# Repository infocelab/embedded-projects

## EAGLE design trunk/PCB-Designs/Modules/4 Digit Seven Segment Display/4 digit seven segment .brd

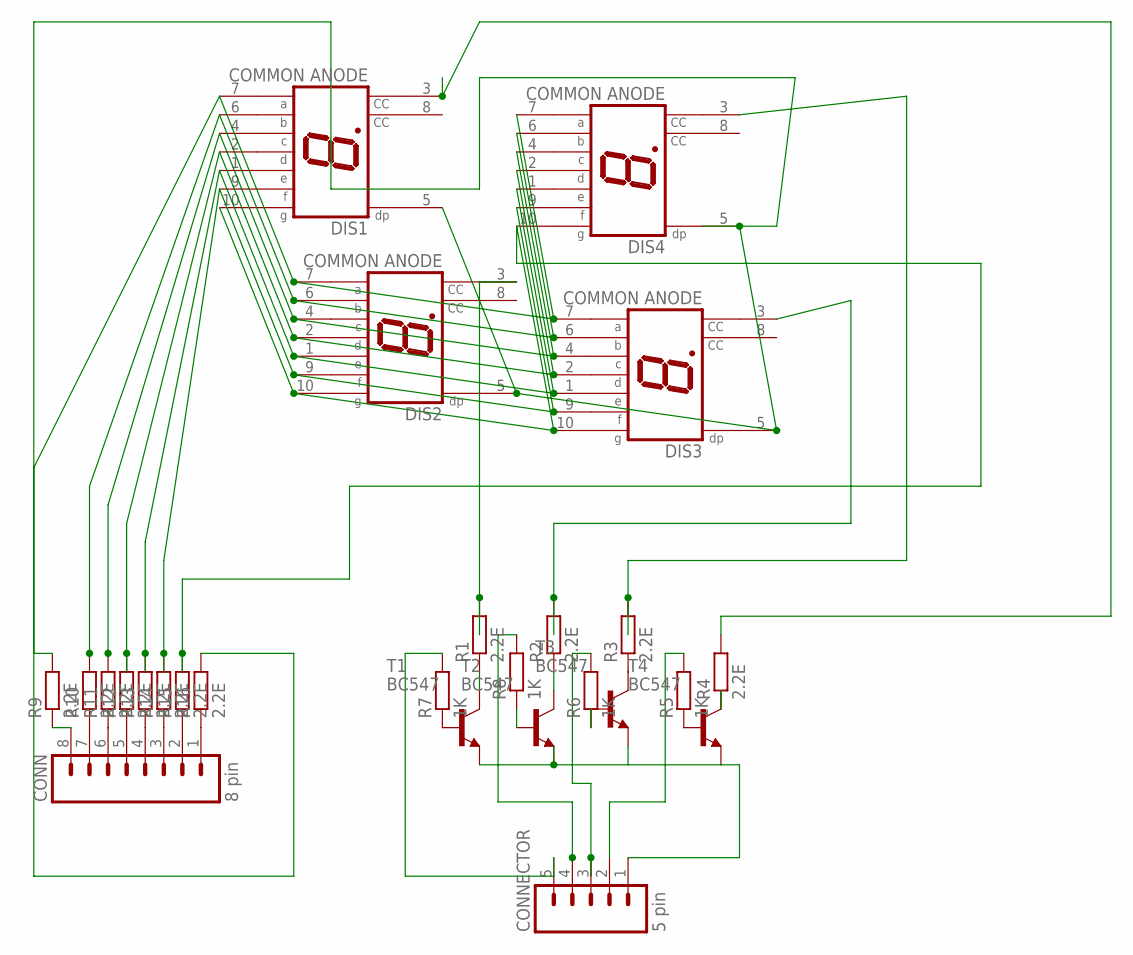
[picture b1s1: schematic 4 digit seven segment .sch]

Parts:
CONN: 8 pin; 08P
CONNECTOR: 5 pin; 05P
DIS1, DIS2, DIS3, DIS4: COMMON ANODE; HDSP-M
R1, R2, R3, R4, R9, R10, R11, R12, R13, R14, R15, R16: 2.2E; 0204/7
R5, R6, R7, R8: 1K; 0204/7
T1, T2, T3, T4: BC547; TO92

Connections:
unnamed: CONNECTOR.4, R8.2
unnamed: DIS1.9 (F), DIS2.9 (F), DIS3.9 (F), DIS4.9 (F), R14.2
unnamed: DIS1.2 (D), DIS2.2 (D), DIS3.2 (D), DIS4.2 (D), R12.2
unnamed: DIS1.6 (B), DIS2.6 (B), DIS3.6 (B), DIS4.6 (B), R10.2
unnamed: DIS1.7 (A), DIS2.7 (A), DIS3.7 (A), DIS4.7 (A), R9.2
unnamed: DIS3.3 (CC), R2.2
unnamed: DIS1.4 (C), DIS2.4 (C), DIS3.4 (C), DIS4.4 (C), R11.2
unnamed: DIS1.1 (E), DIS2.1 (E), DIS3.1 (E), DIS4.1 (E), R13.2
unnamed: CONNECTOR.3, R6.2
unnamed: R1.1, T1.3 (C)
unnamed: R2.1, T2.3 (C)
unnamed: R3.1, T3.3 (C)
unnamed: R4.1, T4.3 (C)
unnamed: R5.1, T4.2 (B)
unnamed: R6.1, T3.2 (B)
unnamed: R7.1, T1.2 (B)
unnamed: R8.1, T2.2 (B)
unnamed: CONN.8, R9.1
unnamed: CONN.7, R10.1
unnamed: CONN.6, R11.1
unnamed: CONN.4, R13.1
unnamed: CONN.3, R14.1
unnamed: CONN.2, R15.1
unnamed: CONN.1, R16.1
unnamed: CONN.5, R12.1
unnamed: DIS1.10 (G), DIS2.10 (G), DIS3.10 (G), DIS4.10 (G), R15.2
unnamed: DIS1.5 (DP), DIS2.5 (DP), DIS3.5 (DP), DIS4.5 (DP), R16.2
unnamed: CONNECTOR.5, R7.2
unnamed: CONNECTOR.2, R5.2
unnamed: CONNECTOR.1, T1.1 (E), T2.1 (E), T3.1 (E), T4.1 (E)
unnamed: DIS1.3 (CC), R4.2
unnamed: DIS4.3 (CC), R3.2
unnamed: DIS2.3 (CC), R1.2

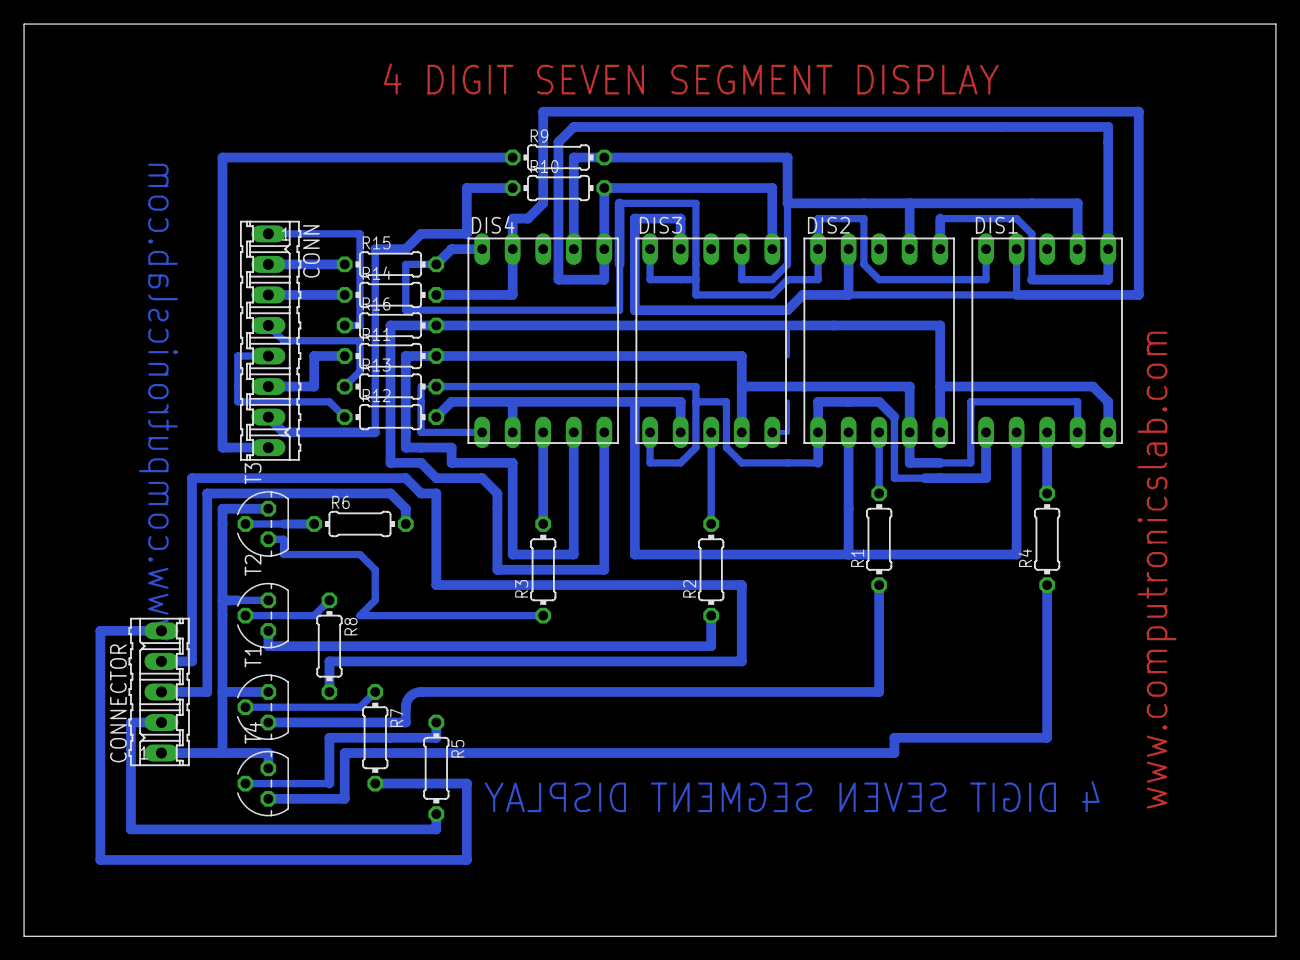
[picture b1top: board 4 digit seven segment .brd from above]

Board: 2 copper layers, 104.1 x 75.9 mm, 26 parts (0 on the bottom side), 33 nets.

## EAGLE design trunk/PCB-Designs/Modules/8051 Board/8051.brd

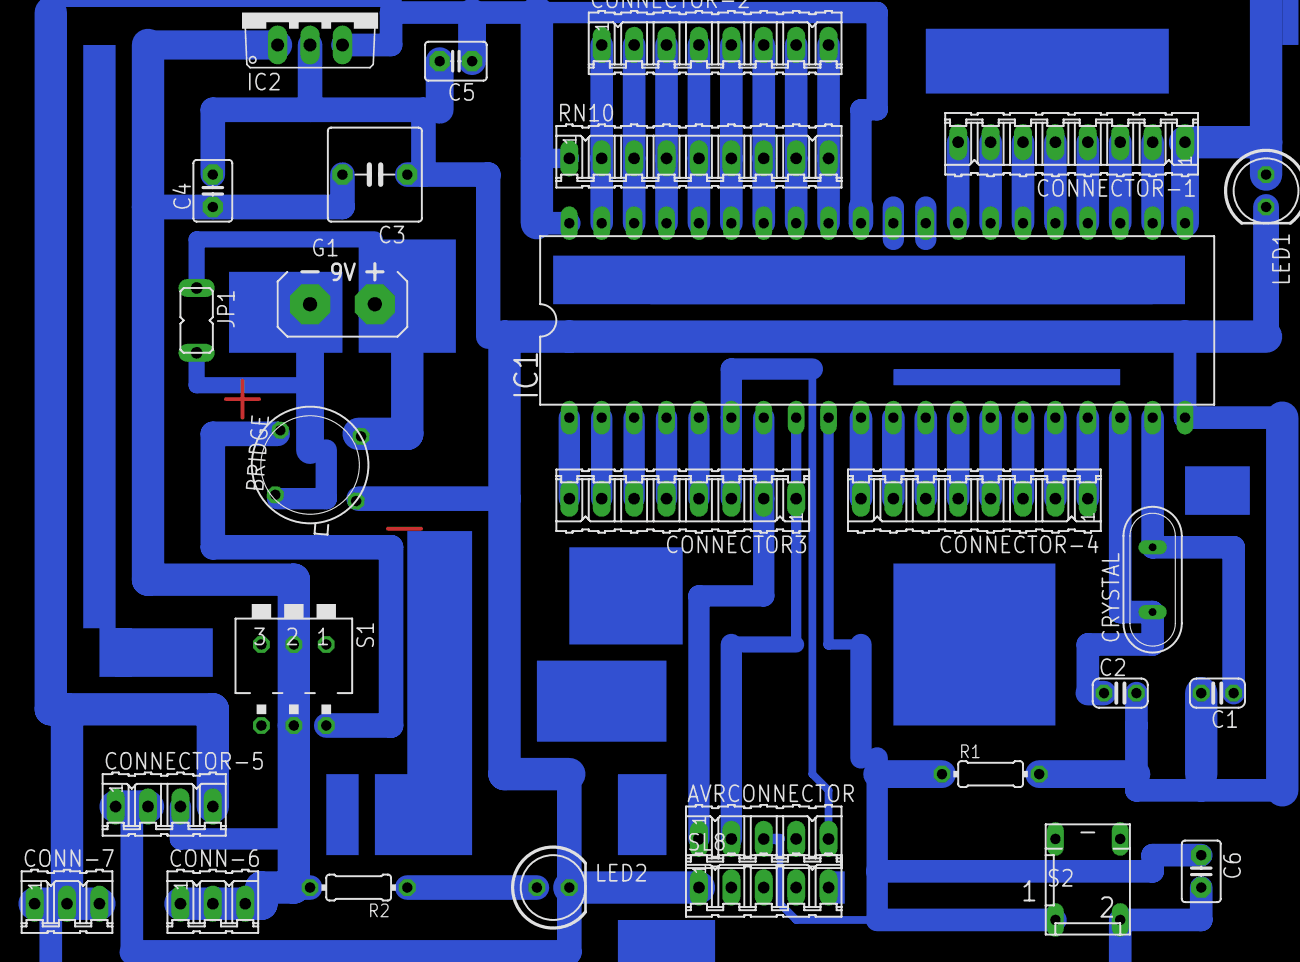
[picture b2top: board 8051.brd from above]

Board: 2 copper layers, 28 parts (0 on the bottom side), 42 nets.

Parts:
AVRCONNECTOR: 05P
BRIDGE: TO39/4
C1, C2: 33pf; C025-024X044
C3: 470uf; C5B7.2
C4: .01uf; C2.5-3
C5: 4.7uf; C2.5-3
C6: 0.1uf; C2.5-3
CONN-6, CONN-7: 3 pin; 03P
CONNECTOR3: 8 pin; 08P
CONNECTOR-1, CONNECTOR-2, CONNECTOR-4: 8 pin; 08P
CONNECTOR-5: 4 pin; 04P
CRYSTAL: 11.0592 mhz; QS
G1: AB9V
IC1: AT89S51; DIL40
IC2: 7805TV; TO220V
JP1: TRANSFORMER; JP1
LED1, LED2: 5mm; LED5MM
R1: 10k; 0204/7
R2: 560E; 0204/7
RN10: 10 k; 09P
S1: DA-03
S2: push switch; DP-02
SL8: 05P

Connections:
unnamed: C2.1, CRYSTAL.1, IC1.18
unnamed: C1.1, CRYSTAL.2, IC1.19
unnamed: C3.2, C4.1, CONN-6.1, CONN-6.2, CONN-6.3, CONNECTOR-5.3, IC2.1, R2.2, S1.5
unnamed: BRIDGE.2, G1.+, JP1.1
unnamed: CONNECTOR-4.8, IC1.10
unnamed: CONNECTOR-4.7, IC1.11
unnamed: CONNECTOR-4.6, IC1.12
unnamed: CONNECTOR-4.5, IC1.13
unnamed: CONNECTOR-4.4, IC1.14
unnamed: CONNECTOR-4.3, IC1.15
unnamed: CONNECTOR-4.2, IC1.16
unnamed: CONNECTOR-4.1, IC1.17
unnamed: AVRCONNECTOR.3, C6.1, IC1.9, R1.1, S2.1
unnamed: AVRCONNECTOR.1, CONNECTOR3.2, IC1.7
unnamed: BRIDGE.4, G1.-, JP1.2
unnamed: CONNECTOR3.4, IC1.5
unnamed: CONNECTOR3.5, IC1.4
unnamed: CONNECTOR3.6, IC1.3
unnamed: CONNECTOR3.7, IC1.2
unnamed: CONNECTOR3.8, IC1.1
unnamed: CONNECTOR-2.1, IC1.39, RN10.2
unnamed: CONNECTOR-2.2, IC1.38, RN10.3
unnamed: CONNECTOR-2.3, IC1.37, RN10.4
unnamed: CONNECTOR-2.4, IC1.36, RN10.5
unnamed: CONNECTOR-2.5, IC1.35, RN10.6
unnamed: CONNECTOR-2.6, IC1.34, RN10.7
unnamed: CONNECTOR-2.7, IC1.33, RN10.8
unnamed: CONNECTOR-2.8, IC1.32, RN10.9
unnamed: CONNECTOR-1.1, IC1.21, LED1.A
unnamed: CONNECTOR-1.2, IC1.22
unnamed: CONNECTOR-1.3, IC1.23
unnamed: CONNECTOR-1.4, IC1.24
unnamed: CONNECTOR-1.5, IC1.25
unnamed: CONNECTOR-1.6, IC1.26
unnamed: CONNECTOR-1.7, IC1.27
unnamed: CONNECTOR-1.8, IC1.28
unnamed: C5.1, C6.2, CONN-7.1, CONN-7.2, CONN-7.3, CONNECTOR-5.4, IC1.31, IC1.40, IC2.3, RN10.1, S2.2
unnamed: BRIDGE.1, C1.2, C2.2, C3.1, C4.2, C5.2, CONNECTOR-5.1, CONNECTOR-5.2, IC1.20, IC2.2, LED1.K, LED2.K, R1.2, SL8.1
unnamed: AVRCONNECTOR.5, CONNECTOR3.3, IC1.6
unnamed: LED2.A, R2.1
unnamed: AVRCONNECTOR.2, CONNECTOR3.1, IC1.8
unnamed: BRIDGE.3, S1.6

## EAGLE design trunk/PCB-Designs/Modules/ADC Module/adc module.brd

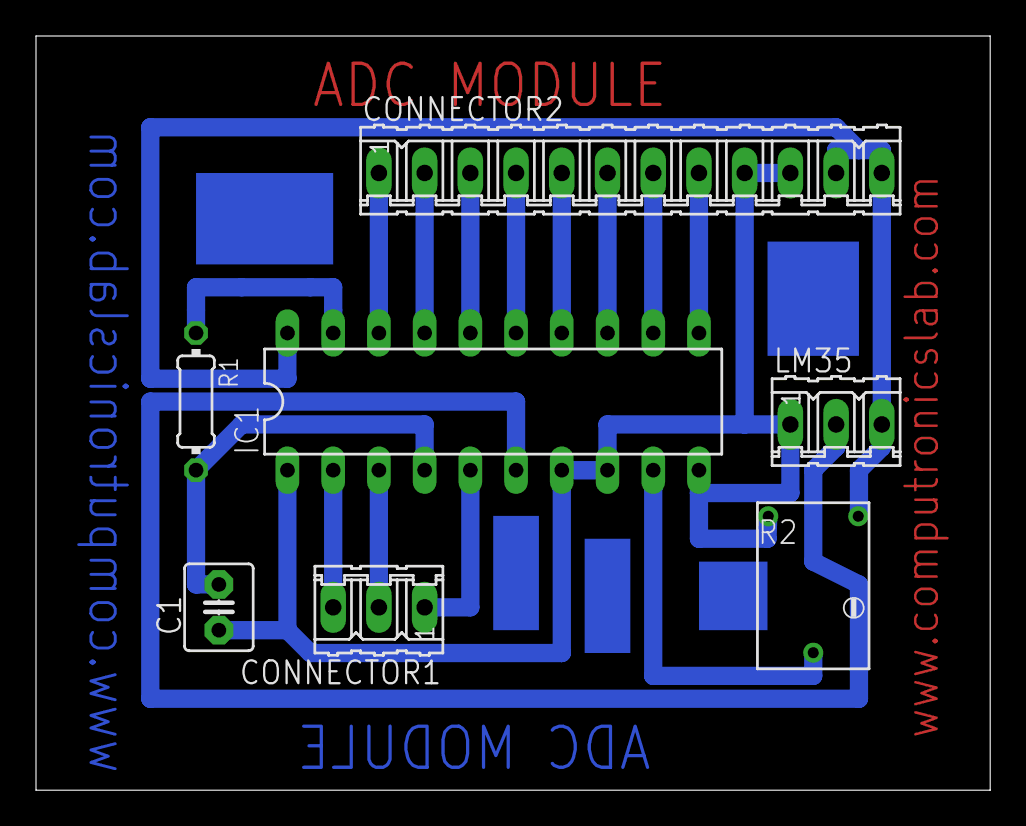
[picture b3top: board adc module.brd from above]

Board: 2 copper layers, 53.0 x 41.9 mm, 7 parts (0 on the bottom side), 17 nets.

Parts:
C1: 150pf; C2.5-4
CONNECTOR1: 3 pin; 03P
CONNECTOR2: 12 pin; 12P
IC1: ADC0804; DIL20
LM35: 3 pin; 03P
R1: 10K; 0204/7
R2: 10K; RTRIM74W

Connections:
unnamed: CONNECTOR2.1, IC1.18
unnamed: CONNECTOR2.2, IC1.17
unnamed: CONNECTOR2.3, IC1.16
unnamed: CONNECTOR2.4, IC1.15
unnamed: CONNECTOR2.5, IC1.14
unnamed: CONNECTOR2.6, IC1.13
unnamed: CONNECTOR2.7, IC1.12
unnamed: CONNECTOR2.8, IC1.11
unnamed: IC1.19, R1.1
unnamed: C1.2, IC1.4, R1.2
unnamed: CONNECTOR1.3, IC1.2
unnamed: CONNECTOR1.2, IC1.3
unnamed: CONNECTOR1.1, IC1.5
unnamed: C1.1, CONNECTOR2.9, CONNECTOR2.10, IC1.1, IC1.7, IC1.8, IC1.10, LM35.1, R2.1
unnamed: IC1.6, LM35.2
unnamed: IC1.9, R2.2
unnamed: CONNECTOR2.11, CONNECTOR2.12, IC1.20, LM35.3, R2.3

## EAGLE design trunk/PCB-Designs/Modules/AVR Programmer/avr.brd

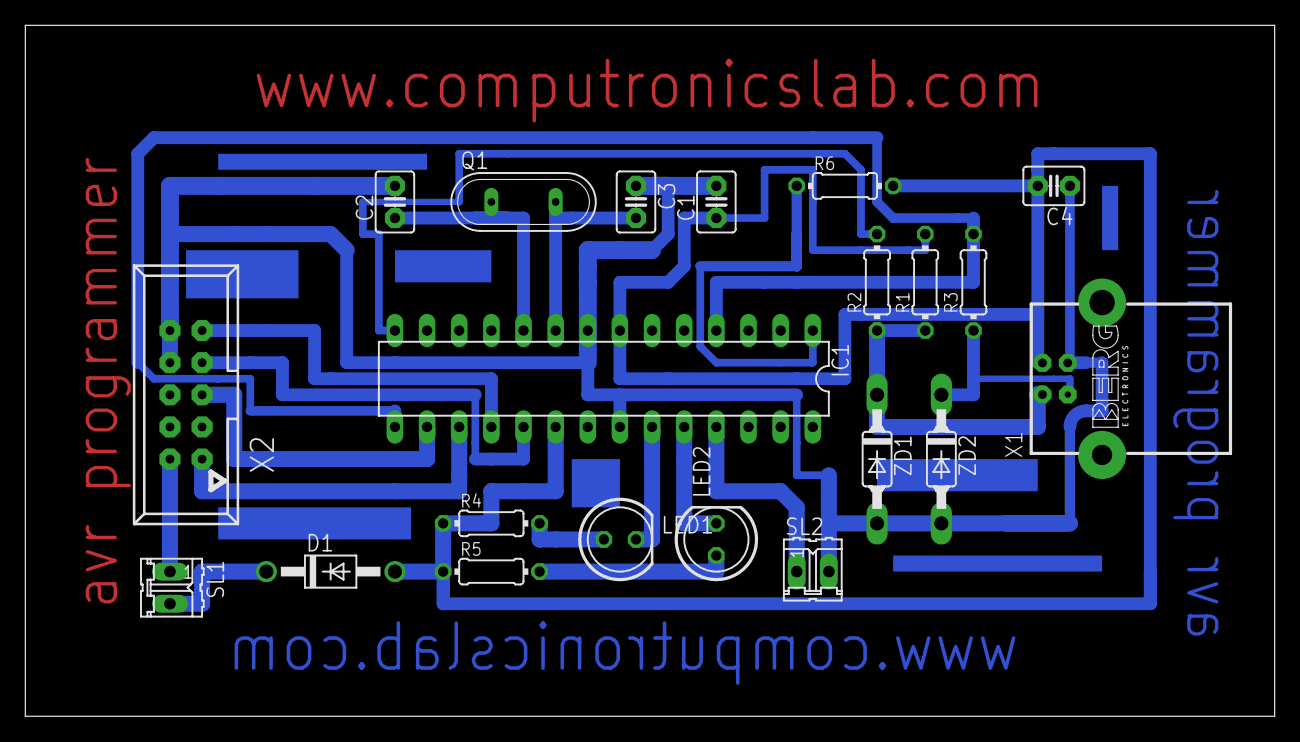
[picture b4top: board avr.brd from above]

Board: 2 copper layers, 98.7 x 54.6 mm, 21 parts (0 on the bottom side), 20 nets.

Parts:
C1: 0.1uf; C2.5-3
C2, C3: 22pf; C2.5-3
C4: 10uf; C2.5-3
D1: 1N4007; DO41-10
IC1: QT9701BD; DIL28-3
LED1, LED2: 5mm; LED5MM
Q1: 12 MHZ; QS
R1: 2.6k; 0204/7
R2, R3: 70E; 0204/7
R4, R5: 1K; 0204/7
R6: 10K; 0204/7
SL1, SL2: jumper; 02P
X1: PN61729-S
X2: avr conn; 057-010-1
ZD1, ZD2: 3.6v; SOD81

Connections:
unnamed: C3.2, IC1.9, Q1.2
unnamed: C2.1, IC1.10, Q1.1
unnamed: IC1.1, R6.1
unnamed: R1.1, R2.1, X1.2, ZD1.C
unnamed: C1.2, C2.2, C3.1, C4.1, IC1.8, IC1.22, SL2.2, X1.4, X2.8, X2.10, ZD1.A, ZD2.A
unnamed: IC1.14, R2.2
unnamed: R3.1, X1.3, ZD2.C
unnamed: IC1.4, IC1.15, R3.2
unnamed: C1.1, C4.2, D1.A, IC1.7, IC1.20, R1.2, R4.1, R5.1, R6.2, X1.1
unnamed: IC1.24, LED2.K
unnamed: D1.C, SL1.2
unnamed: IC1.23, LED1.K
unnamed: LED2.A, R5.2
unnamed: SL1.1, X2.2
unnamed: IC1.17, X2.1
unnamed: IC1.16, X2.5
unnamed: IC1.19, X2.7
unnamed: IC1.18, X2.9
unnamed: IC1.25, SL2.1
unnamed: LED1.A, R4.2

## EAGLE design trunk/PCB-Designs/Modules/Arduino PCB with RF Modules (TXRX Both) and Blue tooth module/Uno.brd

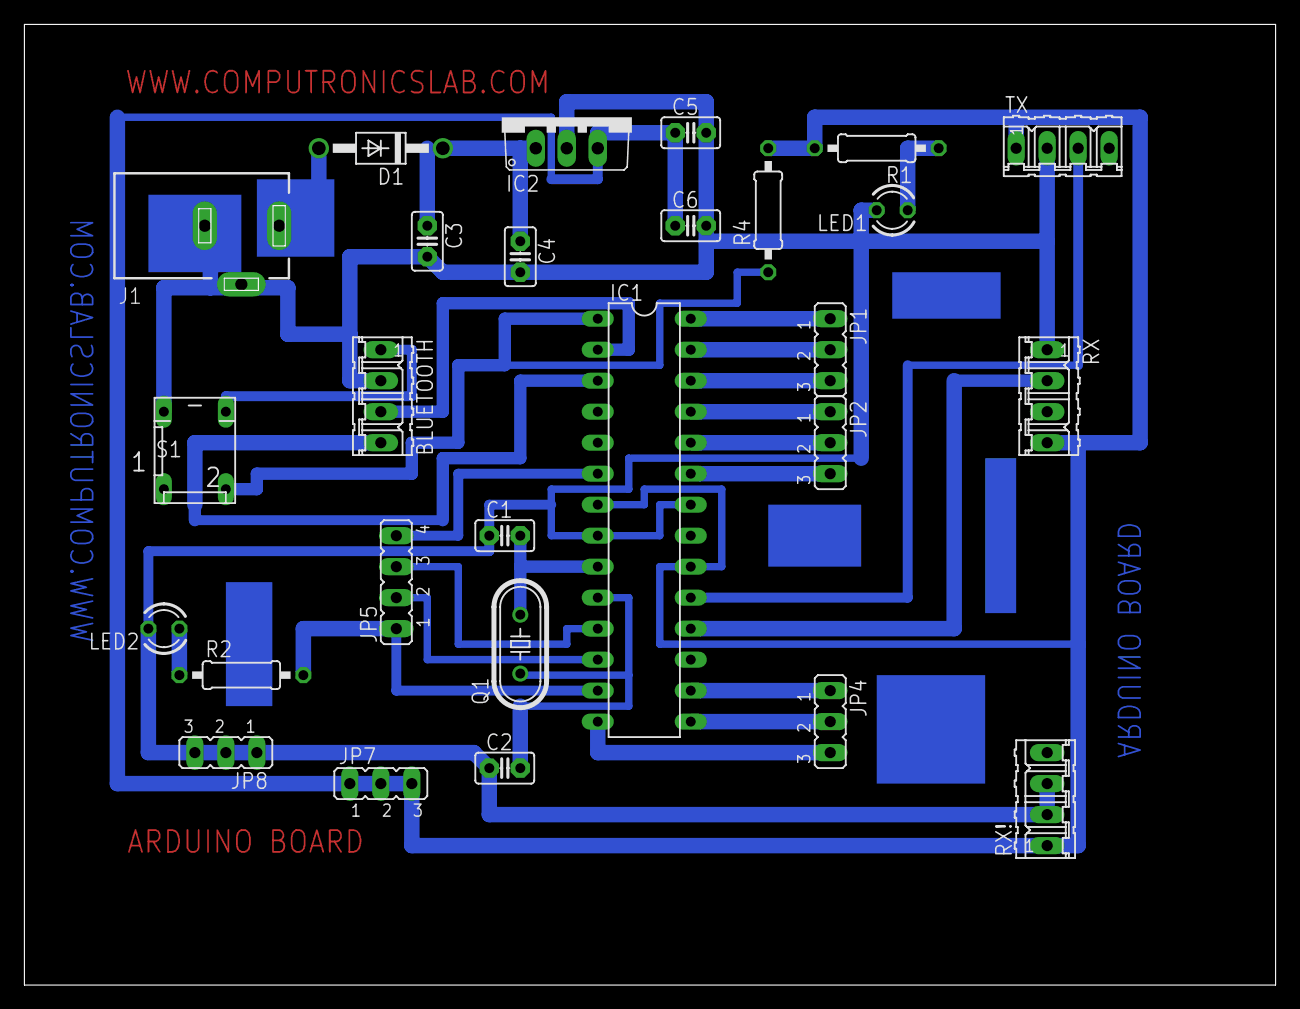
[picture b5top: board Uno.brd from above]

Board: 2 copper layers, 102.5 x 78.7 mm, 27 parts (0 on the bottom side), 27 nets.

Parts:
BLUETOOTH: 04P
C1, C2: 22pf; C2.5-2
C3: 100UF; C2.5-2
C4, C5: 0.1uf; C2.5-2
C6: 4.7uf; C2.5-2
D1: 1N4007; DO41-10
IC1: ATMEGA328; DIL28-3
IC2: 7805; TO220V
J1: DCJ0303
JP1, JP2, JP4, JP7, JP8: JP2
JP5: JP4
LED1, LED2: LED3MM
Q1: 12MHZ; HC49/S
R1: 220R; 0207/10
R2: 330R; 0207/10
R4: 10K; 0207/10
RX: 04P
RX!: 04P
S1: DP-02
TX: 04P

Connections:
unnamed: C1.2, IC1.9, Q1.2
unnamed: C2.2, IC1.10, Q1.1
unnamed: D1.A, J1.1
unnamed: C5.1, C6.1, IC1.7, IC1.20, IC2.3, JP7.1, JP7.2, JP7.3, R1.2, R4.2, RX.4, RX!.1, TX.1
unnamed: BLUETOOTH.2, C1.1, C2.1, C3.2, C4.2, C5.2, C6.2, IC1.8, IC1.22, IC2.2, J1.2, J1.3, JP8.1, JP8.2, JP8.3, LED1.K, LED2.K, RX.1, RX!.2, RX!.3, S1.4, TX.2
unnamed: LED1.A, R1.1
unnamed: C3.1, C4.1, D1.C, IC2.1
unnamed: IC1.28, JP1.1
unnamed: IC1.27, JP1.2
unnamed: IC1.26, JP1.3
unnamed: IC1.25, JP2.1
unnamed: IC1.24, JP2.2
unnamed: IC1.23, JP2.3
unnamed: BLUETOOTH.3, IC1.2
unnamed: BLUETOOTH.1, S1.3
unnamed: BLUETOOTH.4, IC1.3
unnamed: IC1.6, JP5.4
unnamed: IC1.12, JP5.2
unnamed: IC1.11, JP5.3
unnamed: IC1.13, JP5.1, R2.2
unnamed: IC1.14, JP4.3
unnamed: IC1.15, JP4.2
unnamed: IC1.16, JP4.1
unnamed: IC1.18, RX.2
unnamed: IC1.19, TX.3
unnamed: IC1.1, R4.1, S1.2
unnamed: LED2.A, R2.1
